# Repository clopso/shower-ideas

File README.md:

# 🚿 Shower ideas

Ideas i had while i was taking a shower!  
> Some of these project ideas and inspirations from other people, all credits will be given.

## Summary

- [Ideas](#ideas)
	- [IoT](#iot)
	- [Hobbies](#hobbies)

## Ideas

### IoT

| Project       |                       Description                       |
|:------------- |:-------------------------------------------------------:|
| [Ceiling light](./iot-ceiling-light/) | Make a IoT ceiling ring light with white and RGB colors |

### Hobbies

| Project                                  |                         Description                         |
|:---------------------------------------- |:-----------------------------------------------------------:|
| [F22 RC Airplane](./f22-rc-airplane/)    | A remote control cardboard airplane with ESP32 and NRF24L01 |
| [PC Smart Screen](./pc-smart-screen)     | A mini monitor to connect with your computer.               |
| [Snooker Table Cam](./snooker-table-cam) | A camera on top of a snooker table to capture highlights.   |

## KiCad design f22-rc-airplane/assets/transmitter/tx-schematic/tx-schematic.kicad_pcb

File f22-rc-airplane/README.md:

# ✈️ F22 RC Airplane

> This project was inspired by these two projects: [Cardboard RC Airplane - F22 Raptor](https://youtu.be/WKkWElvF-a0) and [Simple RC Airplane](https://www.youtube.com/watch?v=9SMyBN-B3Vo).

## Table of contents

  - [Idea](#idea)
  - [Materials](#materials)
	  - [Airplane](#airplane)
	  - [Controller](#controller)
  - [Images](#images)
  - [Code](#code)

## Idea

Make a remote control cardboard airplane with ESP32 and NRF24L01.

## Materials

### Airplane
```text
    1x ESP32
    1x ESC
    2x 9gr Micro servos
    1x 7.4V 450Mah LiPo Battery
    1x Brushless dc motor
    1x 108mm Propellers
    1x NRF24L01
```

### Controller
```text
    1x ESP32
    1x NRF24L01
    1x 100uF Capacitor
    2x Joystick
```

## Images

`Coming soon`

## Code

The code was created using the Arduino IDE.  
The airplane and control file is in this [folder](./assets/)

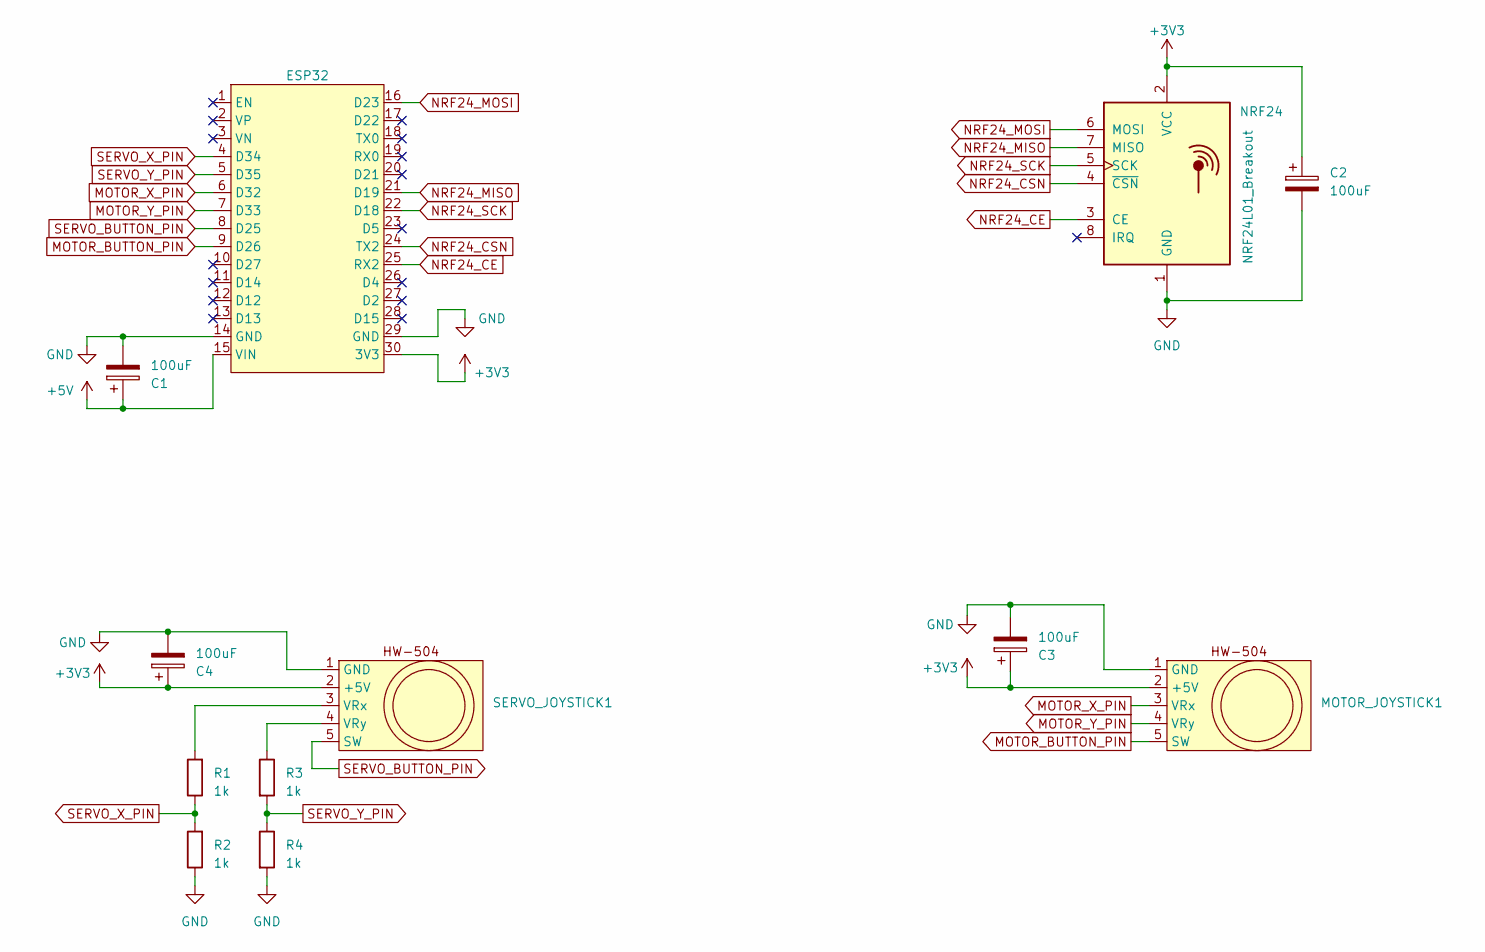
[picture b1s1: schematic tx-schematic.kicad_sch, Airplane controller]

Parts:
C1, C2, C3, C4: 100uF; CP_Radial_D7.5mm_P2.50mm
ESP32: ESP32_30PIN
MOTOR_JOYSTICK1: HW-504
NRF24: NRF24L01_Breakout; nRF24L01_Breakout
R1, R2, R3, R4: 1k; R_Axial_DIN0207_L6.3mm_D2.5mm_P10.16mm_Horizontal
SERVO_JOYSTICK1: HW-504

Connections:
+3V3: C2.1, C3.1, C4.1, ESP32.30 (3V3), MOTOR_JOYSTICK1.2 (+5V), NRF24.2 (VCC), SERVO_JOYSTICK1.2 (+5V)
+5V: C1.1, ESP32.15 (VIN)
GND: C1.2, C2.2, C3.2, C4.2, ESP32.14 (GND), ESP32.29 (GND), MOTOR_JOYSTICK1.1 (GND), NRF24.1 (GND), R2.1, R4.2, SERVO_JOYSTICK1.1 (GND)
MOTOR_BUTTON_PIN: ESP32.9 (D26), MOTOR_JOYSTICK1.5 (SW)
MOTOR_X_PIN: ESP32.6 (D32)
MOTOR_X_PIN: MOTOR_JOYSTICK1.3 (VRx)
MOTOR_Y_PIN: ESP32.7 (D33), MOTOR_JOYSTICK1.4 (VRy)
NRF24_CE: ESP32.25 (RX2), NRF24.3 (CE)
NRF24_CSN: ESP32.24 (TX2), NRF24.4 (~CSN)
NRF24_MISO: ESP32.21 (D19), NRF24.7 (MISO)
NRF24_MOSI: ESP32.16 (D23), NRF24.6 (MOSI)
NRF24_SCK: ESP32.22 (D18), NRF24.5 (SCK)
unnamed: R1.2, SERVO_JOYSTICK1.3 (VRx)
unnamed: R3.1, SERVO_JOYSTICK1.4 (VRy)
SERVO_BUTTON_PIN: ESP32.8 (D25), SERVO_JOYSTICK1.5 (SW)
SERVO_X_PIN: ESP32.4 (D34)
SERVO_X_PIN: R1.1, R2.2
SERVO_Y_PIN: ESP32.5 (D35), R3.2, R4.1

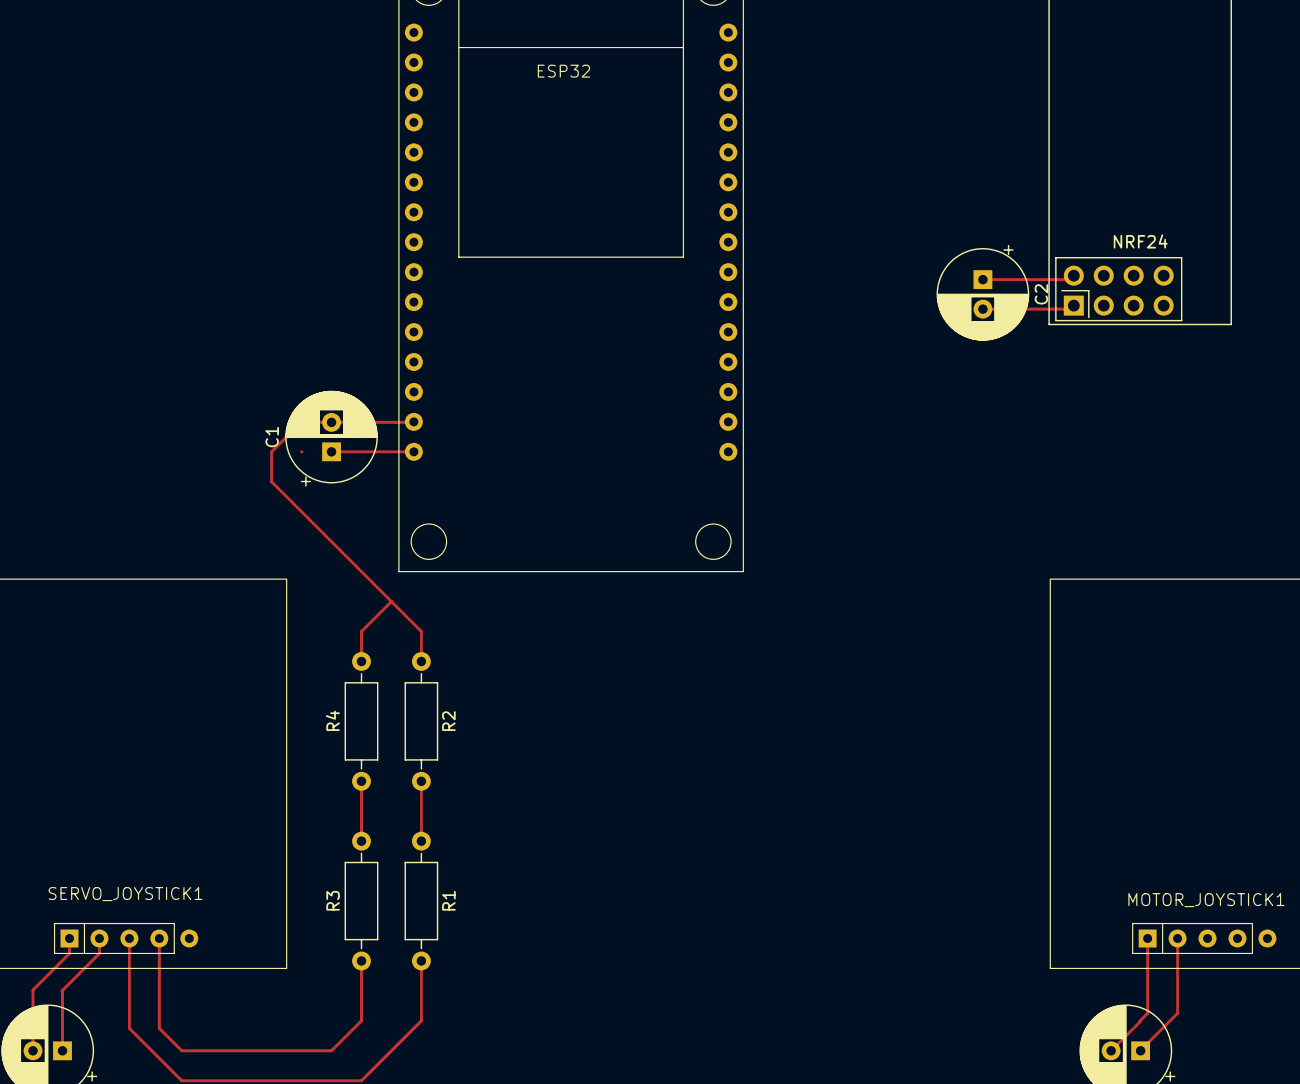
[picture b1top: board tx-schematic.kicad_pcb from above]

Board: 2 copper layers, 12 parts (0 on the bottom side), 15 nets.

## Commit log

2023-05-11 :sparkles: first commit
2023-05-12 💡iot ceiling light idea
2023-05-14 :small_airplane: update f22 code
2023-05-16 :flight_departure: add TX schematic
2023-05-18 :zap: new F22 TX schematic
2023-07-19 :memo: more notes
2023-10-06 ai time show
